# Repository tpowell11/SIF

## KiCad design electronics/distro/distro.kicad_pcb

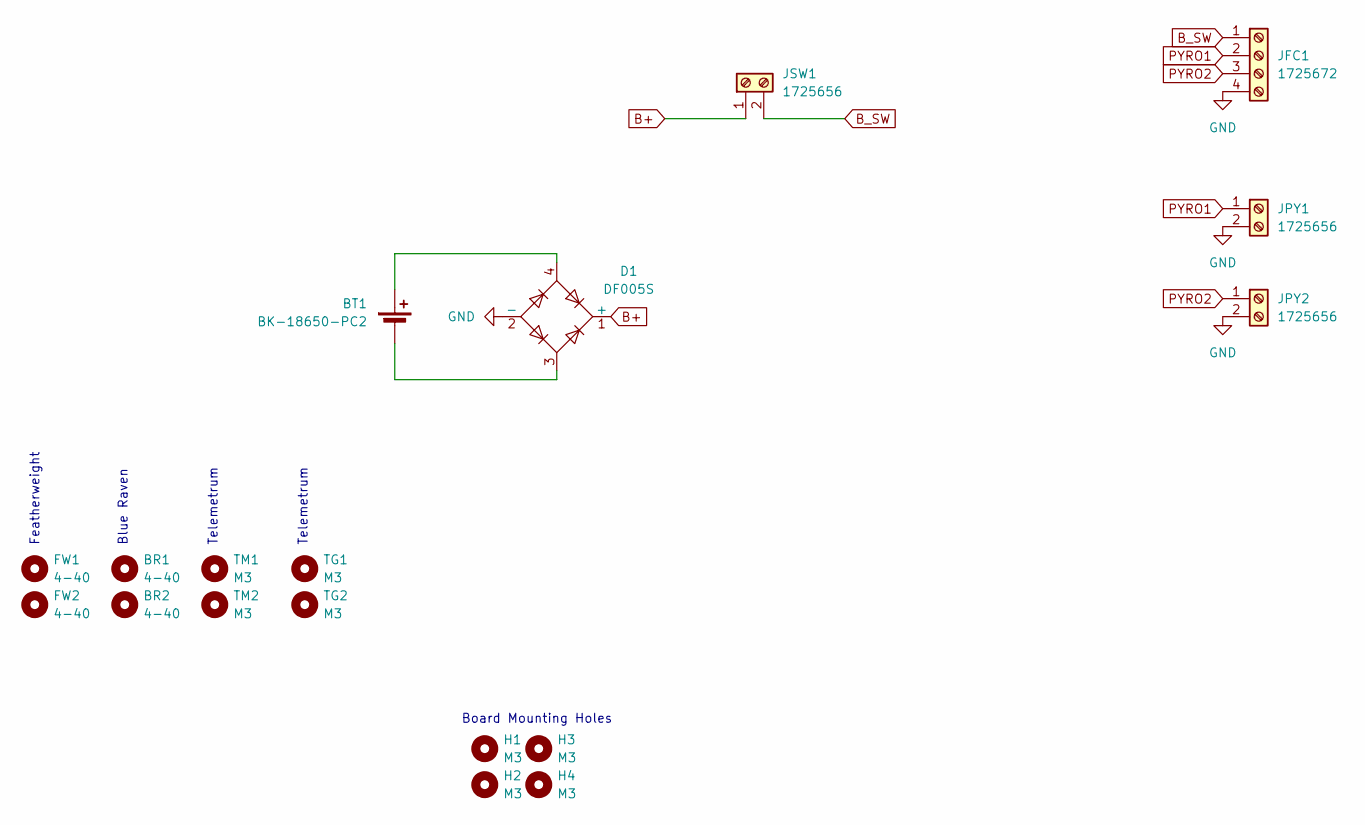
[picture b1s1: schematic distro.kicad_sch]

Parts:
BR1, BR2: 4-40; MountingHole_3.2mm_M3
BT1: BK-18650-PC2; BatteryHolder_MPD_BK-18650-PC2
D1: DF005S; Diode_Bridge_OnSemi_SDIP-4L
FW1, FW2: 4-40; MountingHole_3.2mm_M3
H1, H2, H3, H4: M3; MountingHole_3.2mm_M3
JFC1: 1725672; PinHeader_1x04_P2.54mm_Vertical
JPY1, JPY2: 1725656; PinHeader_1x02_P2.54mm_Vertical
JSW1: 1725656; PinHeader_1x02_P2.54mm_Vertical
TG1, TG2: M3; MountingHole_3.2mm_M3
TM1, TM2: M3; MountingHole_3.2mm_M3

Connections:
B+: D1.1 (+), JSW1.1
B_SW: JFC1.1, JSW1.2
GND: D1.2 (-), JFC1.4, JPY1.2, JPY2.2
unnamed: BT1.1 (+), D1.4
unnamed: BT1.2 (-), D1.3
PYRO1: JFC1.2, JPY1.1
PYRO2: JFC1.3, JPY2.1

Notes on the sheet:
Blue Raven
Telemetrum
Featherweight
Board Mounting Holes

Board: 2 copper layers, 18 parts (1 on the bottom side), 7 nets, no tracks yet.

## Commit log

2024-07-23 files
2024-07-28 newavionics v2, further SIF-1/54M-700 and /54M-1200 work
2024-07-28 avionics v3, preserve addmf settings between iterations, general congfiguragble body setup
2024-08-10 work, made bottail version, modified mandrels and printed
2025-09-29 work
2025-09-29 distro work
